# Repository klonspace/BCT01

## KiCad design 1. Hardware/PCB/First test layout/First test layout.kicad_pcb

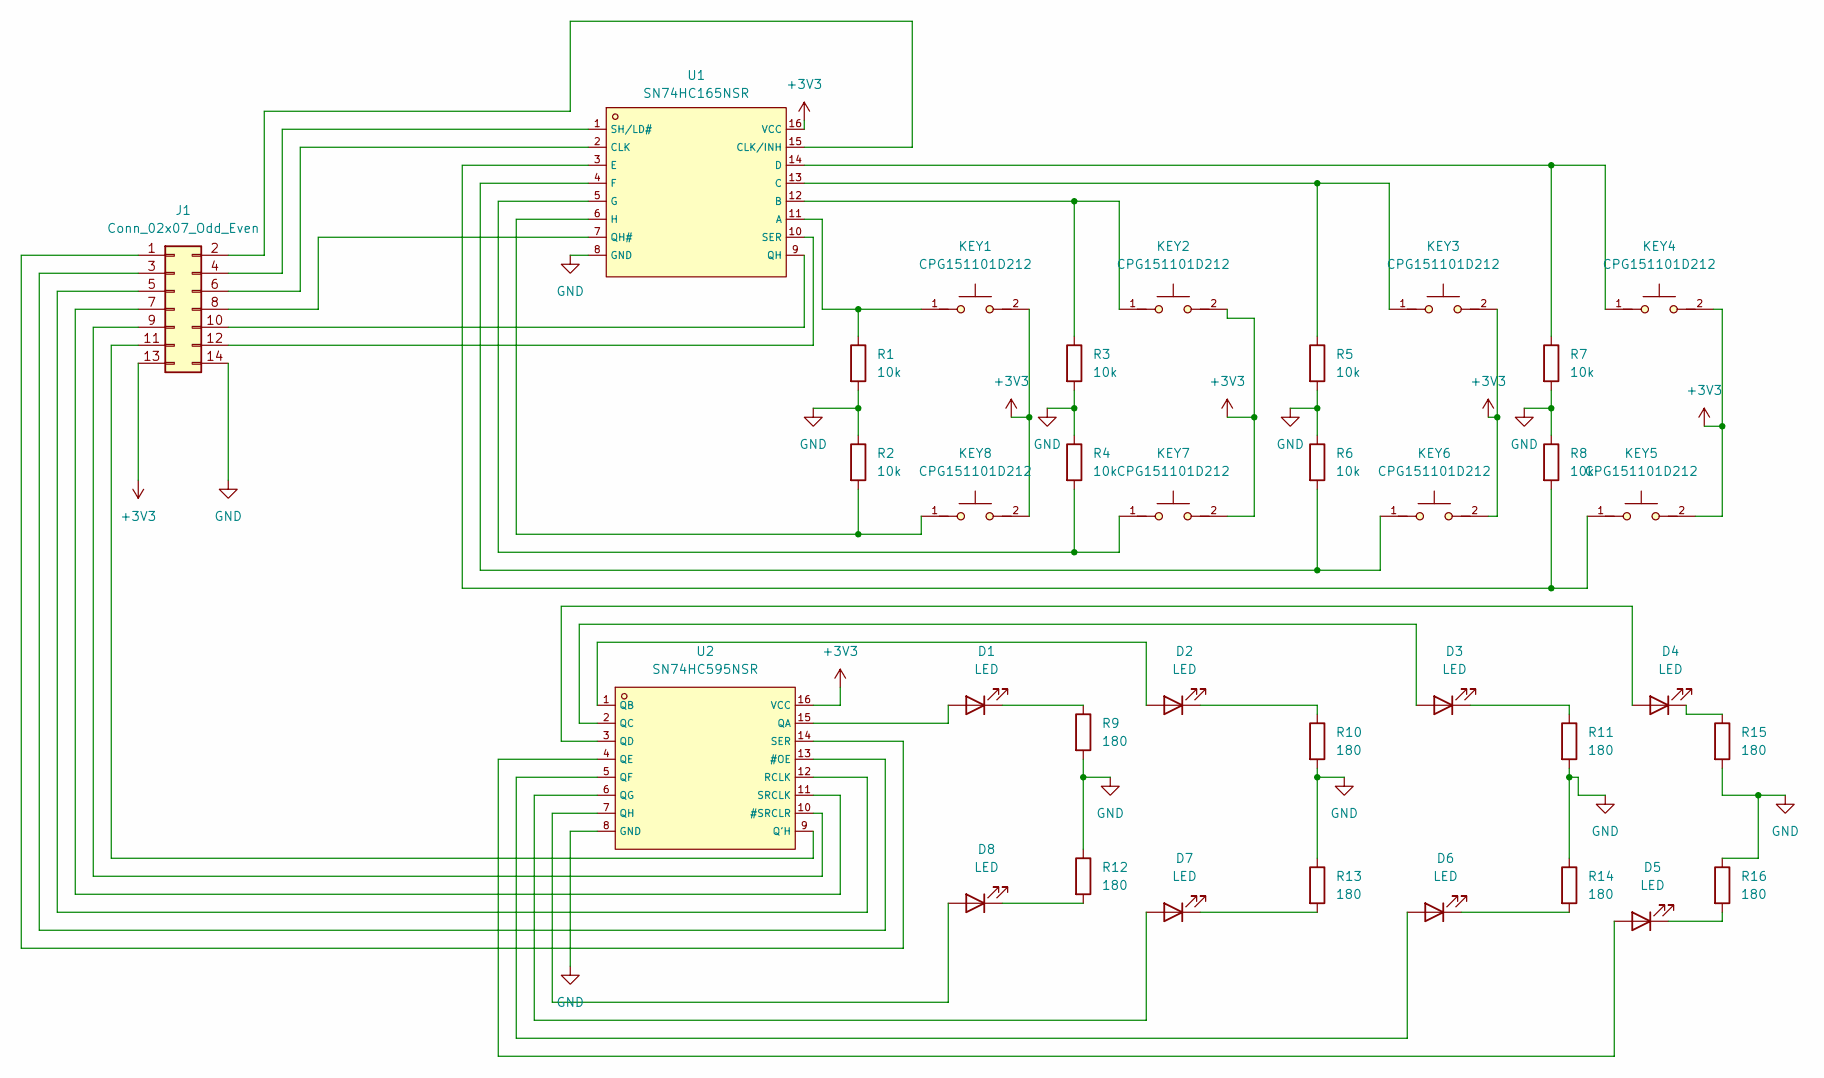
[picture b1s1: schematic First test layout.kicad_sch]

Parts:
D1, D2, D3, D4, D5, D6, D7, D8: LED; LED_1206_3216Metric
J1: Conn_02x07_Odd_Even; PinHeader_2x07_P2.54mm_Vertical_SMD
KEY1, KEY2, KEY3, KEY4, KEY5, KEY6, KEY7, KEY8: CPG151101D212; KEY-TH_CPG151101D21X; LCSC C400234
R1, R2, R3, R4, R5, R6, R7, R8: 10k; R_0201_0603Metric
R9, R10, R11, R12, R13, R14, R15, R16: 180; R_0201_0603Metric
U1: SN74HC165NSR; SOP-16_L10.3-W5.4-P1.27-LS7.8-BL; LCSC C129935
U2: SN74HC595NSR; SOP-16_L10.3-W5.4-P1.27-LS7.8-BL; LCSC C191873

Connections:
+3V3: J1.13, KEY1.2, KEY2.2, KEY3.2, KEY4.2, KEY5.2, KEY6.2, KEY7.2, KEY8.2, U1.16 (VCC), U2.16 (VCC)
GND: J1.14, R1.2, R2.1, R3.2, R4.1, R5.2, R6.1, R7.2, R8.1, R9.2, R10.2, R11.2, R12.1, R13.1, R14.1, R15.2, R16.1, U1.8 (GND), U2.8 (GND)
unnamed: D1.2 (A), U2.15 (QA)
unnamed: D1.1 (K), R9.1
unnamed: D2.2 (A), U2.1 (QB)
unnamed: D2.1 (K), R10.1
unnamed: D3.2 (A), U2.2 (QC)
unnamed: D3.1 (K), R11.1
unnamed: D4.2 (A), U2.3 (QD)
unnamed: D4.1 (K), R15.1
unnamed: D5.2 (A), U2.4 (QE)
unnamed: D5.1 (K), R16.2
unnamed: D6.2 (A), U2.5 (QF)
unnamed: D6.1 (K), R14.2
unnamed: D7.2 (A), U2.6 (QG)
unnamed: D7.1 (K), R13.2
unnamed: D8.2 (A), U2.7 (QH)
unnamed: D8.1 (K), R12.2
unnamed: J1.1, U2.14 (SER)
unnamed: J1.2, U1.15 (CLK/INH)
unnamed: J1.3, U2.13 (#OE)
unnamed: J1.4, U1.1 (SH/LD#)
unnamed: J1.5, U2.12 (RCLK)
unnamed: J1.6, U1.2 (CLK)
unnamed: J1.7, U2.11 (SRCLK)
unnamed: J1.8, U1.7 (QH#)
unnamed: J1.9, U2.10 (#SRCLR)
unnamed: J1.10, U1.9 (QH)
unnamed: J1.11, U2.9 (Q'H)
unnamed: J1.12, U1.10 (SER)
unnamed: KEY1.1, R1.1, U1.11 (A)
unnamed: KEY2.1, R3.1, U1.12 (B)
unnamed: KEY3.1, R5.1, U1.13 (C)
unnamed: KEY4.1, R7.1, U1.14 (D)
unnamed: KEY5.1, R8.2, U1.3 (E)
unnamed: KEY6.1, R6.2, U1.4 (F)
unnamed: KEY7.1, R4.2, U1.5 (G)
unnamed: KEY8.1, R2.2, U1.6 (H)

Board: 2 copper layers, 35 parts (8 on the bottom side), 38 nets, no tracks yet.

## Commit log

2024-01-08 implemented first scratch version, needs improvement
